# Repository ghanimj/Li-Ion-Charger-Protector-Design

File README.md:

# Li-Ion-Charger-Protector-Design
A lithium-ion battery charger, with a built-in short/overcharge/discharge protector

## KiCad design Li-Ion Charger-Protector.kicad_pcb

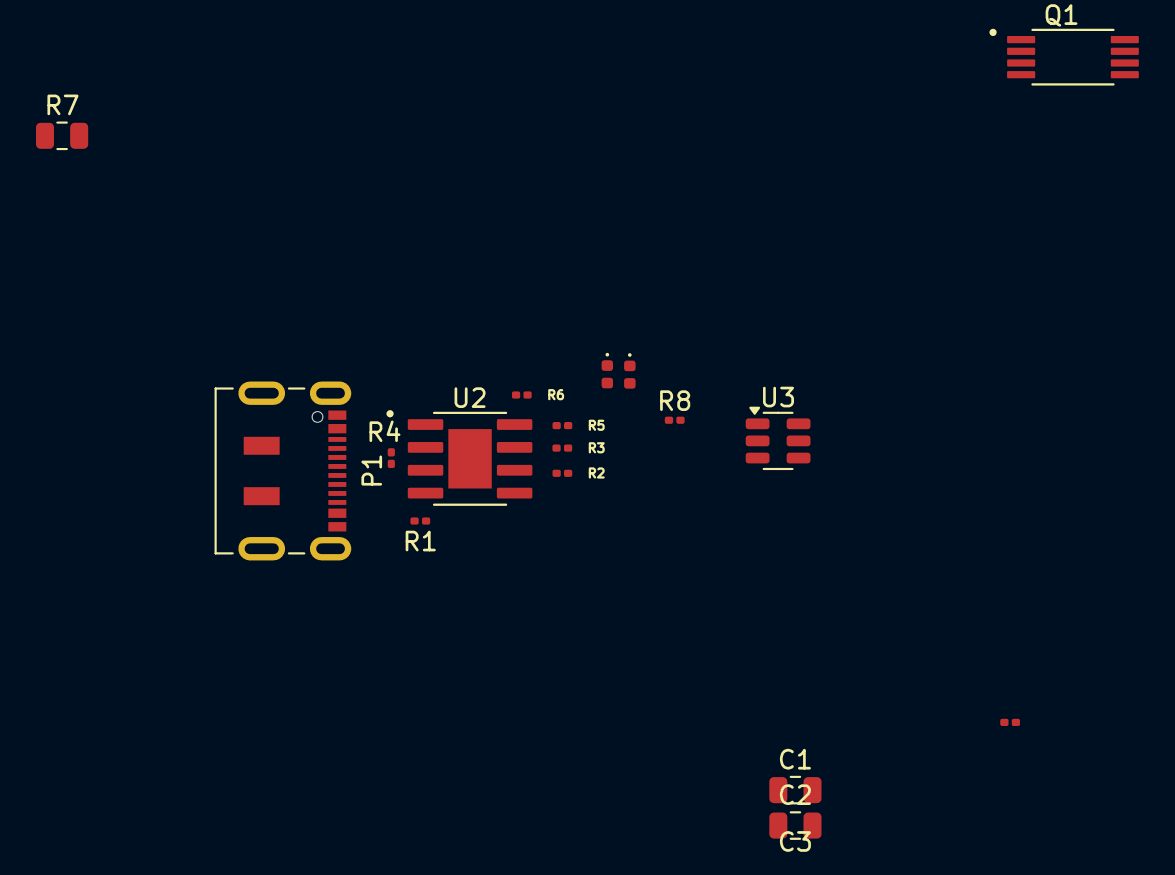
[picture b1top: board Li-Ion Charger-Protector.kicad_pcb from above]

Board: 4 copper layers, 17 parts (0 on the bottom side), 15 nets, no tracks yet.

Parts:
C1, C2: 10uF; C_0805_2012Metric
C3: 0.1uF; C_0201_0603Metric
D1: GREEN; LED_0402_1005Metric
D2: RED; LED_0402_1005Metric
P1: USB_C_Plug_USB2.0; USB_C_Receptacle_JAE_DX07S016JA1R1500
Q1: FS8205A; SOP65P640X120-8N
R1: 0.4; C_0201_0603Metric
R2, R3, R5, R6: 1k; C_0201_0603Metric
R4: 1.2k; C_0201_0603Metric
R7: 2k; C_0805_2012Metric
R8: 100; C_0201_0603Metric
U2: TP4056; SOP127P600X175-9N
U3: DW01A; SOT-23-6

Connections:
+5V: P1.A4 (VBUS), P1.A9 (VBUS), P1.B4 (VBUS), P1.B9 (VBUS), R1.1
/BAT+: C2.1, R8.2, U2.5 (BAT)
GND: C1.1, C2.2, C3.1, P1.A1 (GND), P1.A12 (GND), P1.B1 (GND), P1.B12 (GND), Q1.2, Q1.3, R4.2, R6.1, U2.3 (GND), U3.6 (GND)
unnamed: C1.2, D1.2 (A), D2.2 (A), R1.2, R5.1, R6.2, U2.4 (VCC), U2.8 (CE)
unnamed: D1.1 (K), R3.1
unnamed: D2.1 (K), R2.2
unnamed: Q1.6, Q1.7, R7.2
unnamed: R4.1, U2.2 (PROG)
unnamed: R5.2, U2.1 (TEMP)
unnamed: R3.2, U2.7 (~CHRG)
unnamed: R2.1, U2.6 (~STDBY)
unnamed: R7.1, U3.2 (CS)
unnamed: Q1.5, U3.3 (OC)
unnamed: Q1.4, U3.1 (OD)
unnamed: C3.2, R8.1, U3.5 (VCC)

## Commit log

2026-01-05 Initial PCB layout; needs work
